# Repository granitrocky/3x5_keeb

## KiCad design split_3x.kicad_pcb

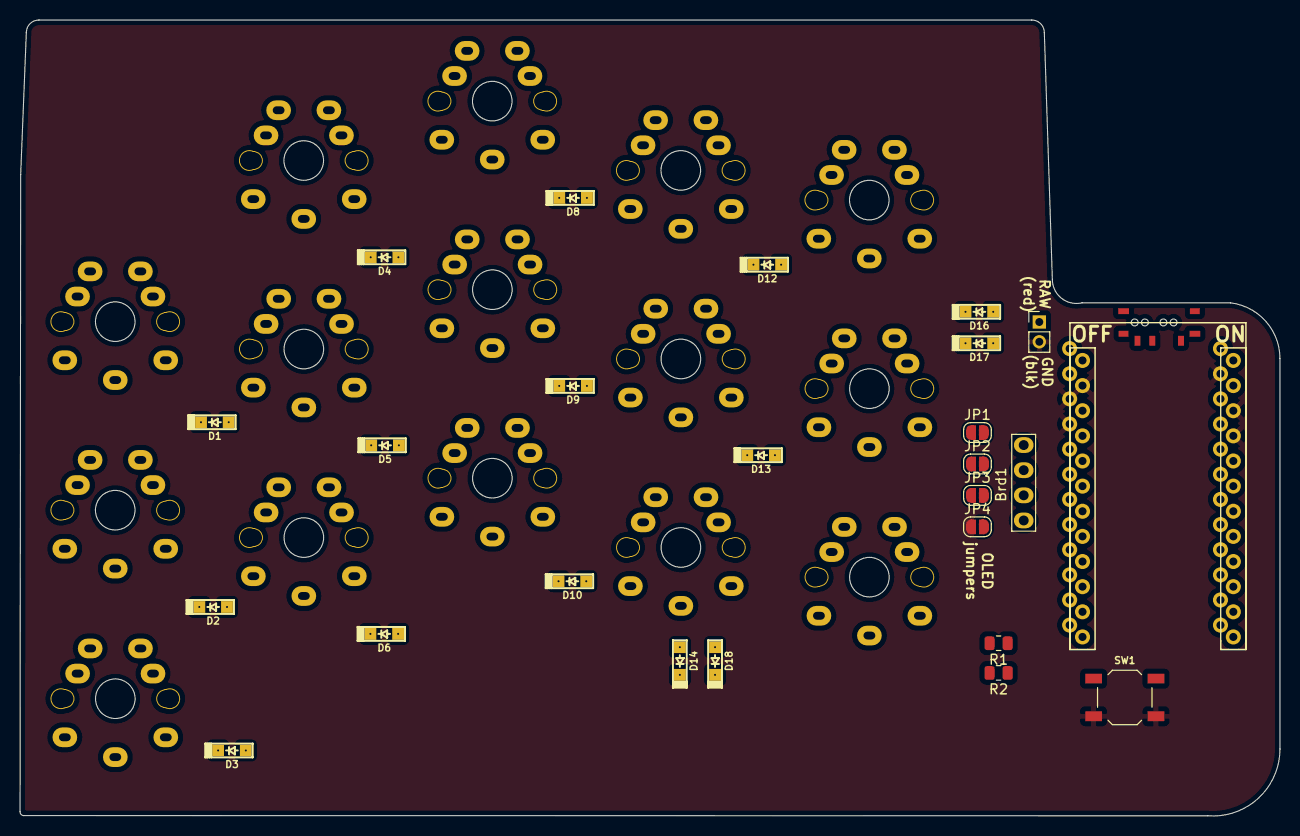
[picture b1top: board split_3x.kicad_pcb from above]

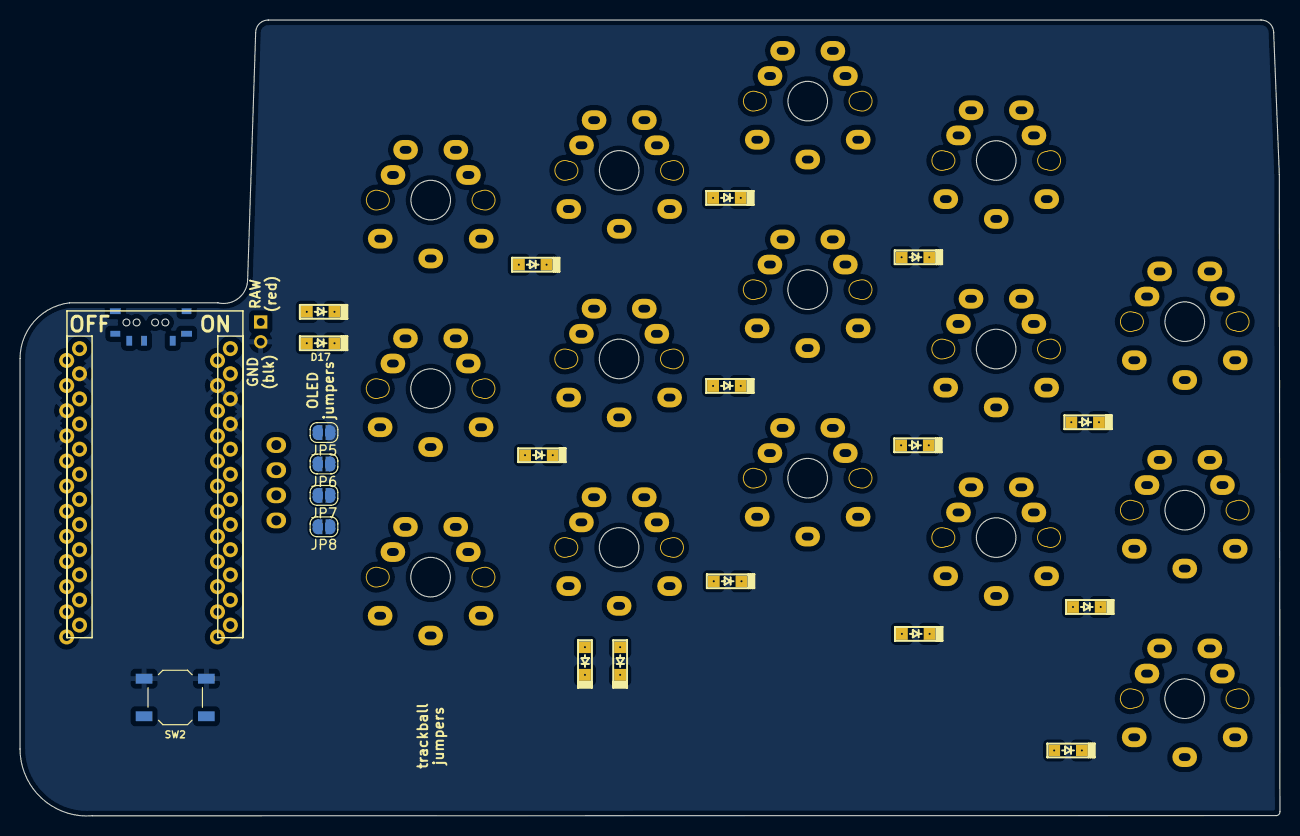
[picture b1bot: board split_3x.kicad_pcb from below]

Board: 2 copper layers, 127.3 x 80.4 mm, 47 parts (6 on the bottom side), 34 nets, no tracks yet.

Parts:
BT1: Bat_loc1; PinHeader_1x02_P2.00mm_Vertical
Brd1: SSD1306; 128x64OLED
D1, D2, D3, D4, D5, D6, D8, D9, D10, D12, D13, D14, D16, D17, D18: D_Small; D_SOD123F
JP1, JP2, JP3, JP4, JP5, JP6, JP7, JP8: Jumper_NO_Small; SolderJumper-2_P1.3mm_Open_RoundedPad1.0x1.5mm
MX1, MX2, MX3, MX4, MX5, MX6, MX7, MX8, MX9, MX11, MX12, MX13, MX15, MX16, MX17: MX-NoLED; CherryMX_Choc_1u_reversible
R1, R2: 4.7k; R_0805_2012Metric
SW1, SW2: SW_Push; SW_SPST_TL3342
SW5, SW6: SW_DIP_x01; switch_MSK-12C02_smd
U1: ProMicro

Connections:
unnamed: BT1.1 (+), SW5.1, SW6.1
unnamed: Brd1.1 (GND), JP4.2, JP8.2
unnamed: Brd1.2 (VCC), JP3.2, JP7.2
unnamed: Brd1.3 (SCL), JP2.2, JP6.2
unnamed: Brd1.4 (SDA), JP1.2, JP5.2
unnamed: D1.2 (A), MX1.2 (ROW)
unnamed: D2.2 (A), MX2.2 (ROW)
unnamed: D3.2 (A), MX3.2 (ROW)
unnamed: D4.2 (A), MX4.2 (ROW)
unnamed: D5.2 (A), MX5.2 (ROW)
unnamed: D6.2 (A), MX6.2 (ROW)
unnamed: D8.2 (A), MX7.2 (ROW)
unnamed: D9.2 (A), MX8.2 (ROW)
unnamed: D10.2 (A), MX9.2 (ROW)
unnamed: D12.2 (A), MX11.2 (ROW)
unnamed: D13.2 (A), MX12.2 (ROW)
unnamed: D14.2 (A), MX13.2 (ROW)
unnamed: D16.2 (A), MX15.2 (ROW)
unnamed: D17.2 (A), MX16.2 (ROW)
unnamed: D18.2 (A), MX17.2 (ROW)
col0: MX1.1 (COL), MX2.1 (COL), MX3.1 (COL), U1.20 (A3/PF4)
col1: MX4.1 (COL), MX5.1 (COL), MX6.1 (COL), U1.19 (A2/PF5)
col2: MX7.1 (COL), MX8.1 (COL), MX9.1 (COL), U1.18 (A1/PF6)
col3: MX11.1 (COL), MX12.1 (COL), MX13.1 (COL), U1.17 (A0/PF7)
col4: MX15.1 (COL), MX16.1 (COL), MX17.1 (COL), U1.16 (15/PB1)
ground: BT1.2 (-), JP4.1, JP5.1, SW1.2, SW2.2, U1.3 (GND), U1.4 (GND), U1.23 (GND)
power: JP3.1, JP6.1, R1.1, R2.1, U1.21 (VCC)
raw: SW5.2, SW6.2, U1.24 (RAW)
reset: SW1.1, SW2.1, U1.22 (RST)
row0: D1.1 (K), D4.1 (K), D8.1 (K), D12.1 (K), D16.1 (K), U1.7 (4/PD4)
row1: D2.1 (K), D5.1 (K), D9.1 (K), D13.1 (K), D17.1 (K), U1.8 (5/PC6)
row2: D3.1 (K), D6.1 (K), D10.1 (K), D14.1 (K), D18.1 (K), U1.9 (6/PD7)
scl: JP2.1, JP7.1, R2.2, U1.6 (3/PD0)
sda: JP1.1, JP8.1, R1.2, U1.5 (2/PD1)
